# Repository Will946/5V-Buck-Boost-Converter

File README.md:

# BckBoost 5V — 5V Buck-Boost Converter

A compact, all-SMD power supply board that delivers a regulated **5 V output** from a wide input voltage range, with reverse-polarity protection via an ideal diode and a power-status LED indicator.

---

## Overview

| Parameter | Value |
|---|---|
| Input voltage (VIN) | 3 V – 16 V |
| Output voltage (VOUT) | 5 V regulated (adjustable range 2.5 V – 9 V) |
| Switching IC | TI TPS63070 buck-boost |
| Reverse-polarity protection | TI LM66200 ideal-diode controller |
| Status indicator | Red 0603 power LED (D1) |
| PCB | ~25 × 23 mm, 3× M2 mounting holes |

---

## How It Works

### Buck-Boost Converter (U1 — TPS63070)

The TPS63070 is a high-efficiency, single-inductor buck-boost converter capable of operating seamlessly whether VIN is above, below, or equal to VOUT. The output is set to 5 V via the resistor-divider feedback network on the FB pin (R1 10 kΩ / R2 68.1 kΩ) and the second divider (R4 365 kΩ) on FB2.

- **Inductor:** L1 — 1.5 µH Coilcraft XFL4020
- **Input capacitors:** C1 (0.1 µF), C2, C3, C9 (10 µF × 3) for filtering and soft-start
- **Output capacitors:** C5, C6 (10 µF + 22 µF), C7, C8 (22 µF × 2) for output regulation and ripple suppression
- **VAUX bypass:** C4 (0.1 µF) on the internal supply rail
- **PS/SYNC pin** (R7, 10 kΩ pull-up) selects power-save mode at light loads for improved efficiency
- **EN pin** (R1, 10 kΩ) is pulled high by default so the converter runs immediately on power-up; bring it low to shut down the converter

The PG (power-good) open-drain output signals when the output is in regulation — this is routed to the connector header and used to drive the power LED circuit.

### Ideal Diode — Reverse Polarity Protection (U2 — LM66200)

The LM66200 acts as an active ideal diode controller. It drives an external MOSFET (the device itself contains the FET) to present a very low forward-voltage drop (~10 mV typical) in the normal forward direction while blocking current completely if the supply is accidentally connected backwards. Compared to a Schottky diode this eliminates the typical 300–500 mV drop and the associated heat, allowing the full input range to reach the converter without power loss.

- VIN1/VIN2 are the input terminals from the external supply
- VOUT of U2 connects to VIN of U1
- The ON pin is tied to VOUT to keep the device always enabled
- Bypass capacitor C8 (22 µF) is placed on the protected output rail

### Power Status LED (D1)

A red 0603 LED is driven from the TPS63070 **PG** (power-good) signal through a current-limiting resistor R6 (1 kΩ). The LED lights up when the output is in regulation, giving a quick visual health-check. R3 (50 kΩ) provides the pull-up for the open-drain PG line.

---

## Connectors

| Reference | Pitch | Function |
|---|---|---|
| J1 | 2 mm, 1×2 | Output — 5 V + GND |
| J2 | 2 mm, 1×2 | Input — VIN + GND |
| J3 | 2 mm, 1×3 | Debug/control header (5Vout, Vin2, St) |
| J4 | 2 mm, 1×3 | Control header (Vin, PG, EN, PS) |

---

## Bill of Materials (key components)

| Ref | Value / Part | Package |
|---|---|---|
| U1 | TPS63070RNMR | 15-pin WQFN (RNM) |
| U2 | LM66200DRLR | SOT-5×3 (DRL) |
| L1 | 1.5 µH — Coilcraft XFL4020 | 4×4 mm SMD |
| C1 | 0.1 µF, 25 V | 0603 |
| C2, C3, C9 | 10 µF, 25 V | 0805 |
| C4 | 0.1 µF, 25 V | 0603 |
| C5 | 10 µF, 25 V | 0805 |
| C6, C7, C8 | 22 µF, 16 V | 0805 |
| R1, R7 | 10 kΩ, 1%, 1/10 W | 0603 |
| R2 | 68.1 kΩ, 1%, 1/10 W | 0603 |
| R4 | 365 kΩ, 1%, 1/10 W | 0603 |
| R6 | 1 kΩ, 1%, 1/10 W | 0603 |
| R3 | 50 kΩ | 0603 |
| D1 | Red LED | 0603 |
| H5–H8 | M2 mounting holes | — |

---

## Schematic & Design Files

| File | Description |
|---|---|
| `5VBuckBoost.kicad_sch` | KiCad 9 Schematic |
| `5VBuckBoost.kicad_pcb` | KiCad 9 PCB Layout |
| `5VBuckBoost.kicad_pro` | KiCad 9 Project File |

---

## Notes

- The output voltage can be changed by adjusting the R1/R2/R4 feedback divider values according to the TPS63070 datasheet formula.
- Do not exceed 16 V on the input. The LM66200's maximum rated VIN is 18 V but the TPS63070 is rated to 16 V, making that the practical system limit.
- All capacitors on the output rail should be X5R or X7R ceramic for stable capacitance across voltage and temperature.
- Designed with KiCad 9

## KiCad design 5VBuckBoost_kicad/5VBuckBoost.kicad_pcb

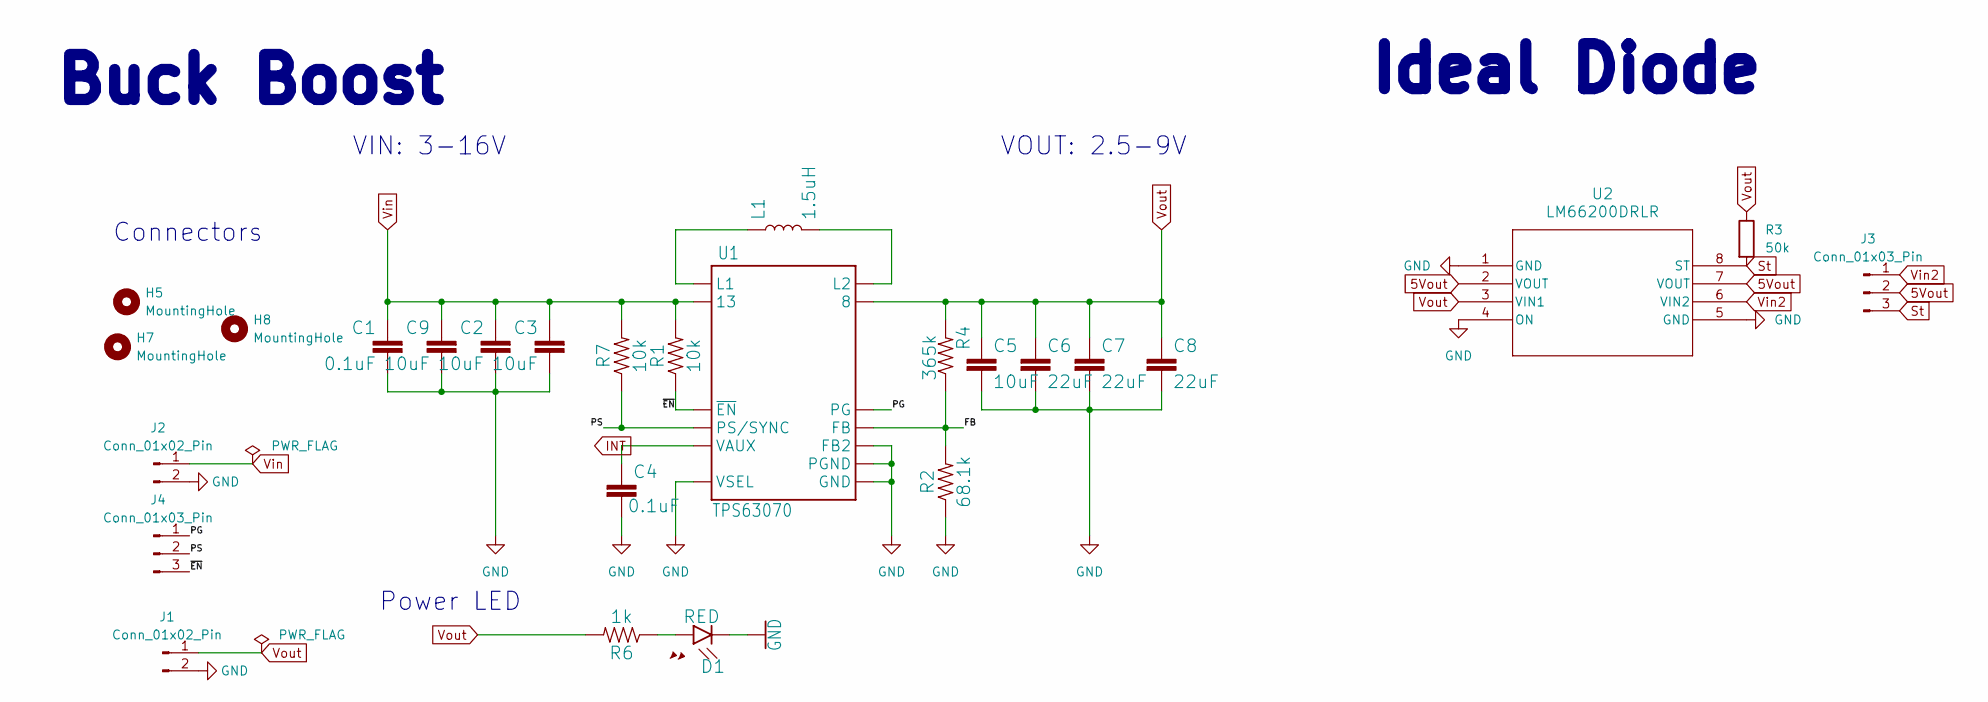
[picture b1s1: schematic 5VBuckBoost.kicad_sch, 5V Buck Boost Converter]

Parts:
C1, C4: 0.1uF; C_0603_1608Metric_Pad1.08x0.95mm_HandSolder
C2, C3, C5, C9: 10uF; C_0805_2012Metric_Pad1.18x1.45mm_HandSolder
C6, C7, C8: 22uF; C_0805_2012Metric_Pad1.18x1.45mm_HandSolder
D1: RED; LED_0603_1608Metric
H5, H7, H8: MountingHole; MountingHole_2.2mm_M2
J1, J2: Conn_01x02_Pin; PinHeader_1x02_P2.00mm_Vertical
J3, J4: Conn_01x03_Pin; PinHeader_1x03_P2.00mm_Vertical
L1: 1.5uH; L_Coilcraft_XxL4020
R1, R7: 10k; R_0603_1608Metric_Pad0.98x0.95mm_HandSolder
R2: 68.1k; R_0603_1608Metric_Pad0.98x0.95mm_HandSolder
R3: 50k; R_0603_1608Metric_Pad0.98x0.95mm_HandSolder
R4: 365k; R_0603_1608Metric_Pad0.98x0.95mm_HandSolder
R6: 1k; R_0603_1608Metric_Pad0.98x0.95mm_HandSolder
U1: TPS63070; RNM0015A
U2: LM66200DRLR; SOT-5X3_DRL_TEX-L

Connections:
5Vout: J3.2, U2.2 (VOUT), U2.7 (VOUT)
/FB: R2.2, R4.1, U1.5 (FB)
/PG: J4.1, U1.2 (PG)
/PS: J4.2, R7.1, U1.1 (PS/SYNC)
/~EN: J4.3, R1.1, U1.14 (~EN)
GND: C1.2, C2.2, C3.2, C4.2, C5.2, C6.2, C7.2, C8.2, C9.2, D1.2 (C), J1.2, J2.2, R2.1, U1.4 (GND), U1.6 (FB2), U1.10 (PGND), U1.15 (VSEL), U2.1 (GND), U2.4 (ON), U2.5 (GND)
unnamed: D1.1 (A), R6.1
unnamed: L1.1, U1.11 (L1)
unnamed: L1.2, U1.9 (L2)
unnamed: C4.1, U1.3 (VAUX)
St: J3.3, R3.2, U2.8 (ST)
Vin: C1.1, C2.1, C3.1, C9.1, J2.1, R1.2, R7.2, U1.12 (13), U1.13
Vin2: J3.1, U2.6 (VIN2)
Vout: C5.1, C6.1, C7.1, C8.1, J1.1, R3.1, R4.2, R6.2, U1.7 (8), U1.8, U2.3 (VIN1)

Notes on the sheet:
Power LED
Connectors
VIN: 3-16V
Buck Boost
Ideal Diode
VOUT: 2.5-9V

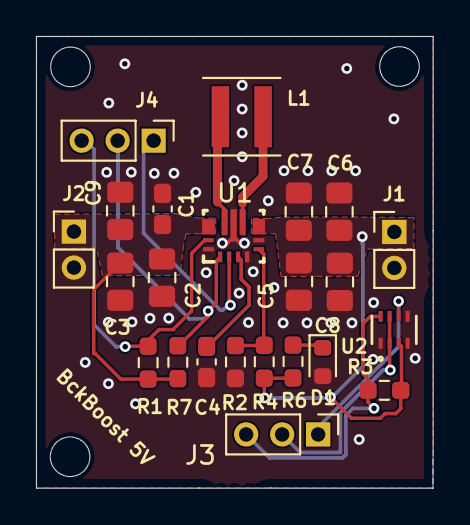
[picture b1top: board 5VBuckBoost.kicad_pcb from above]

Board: 2 copper layers, 22.0 x 25.1 mm, 26 parts (0 on the bottom side), 14 nets.

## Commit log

2026-05-07 Rename READMD.md to README.md
